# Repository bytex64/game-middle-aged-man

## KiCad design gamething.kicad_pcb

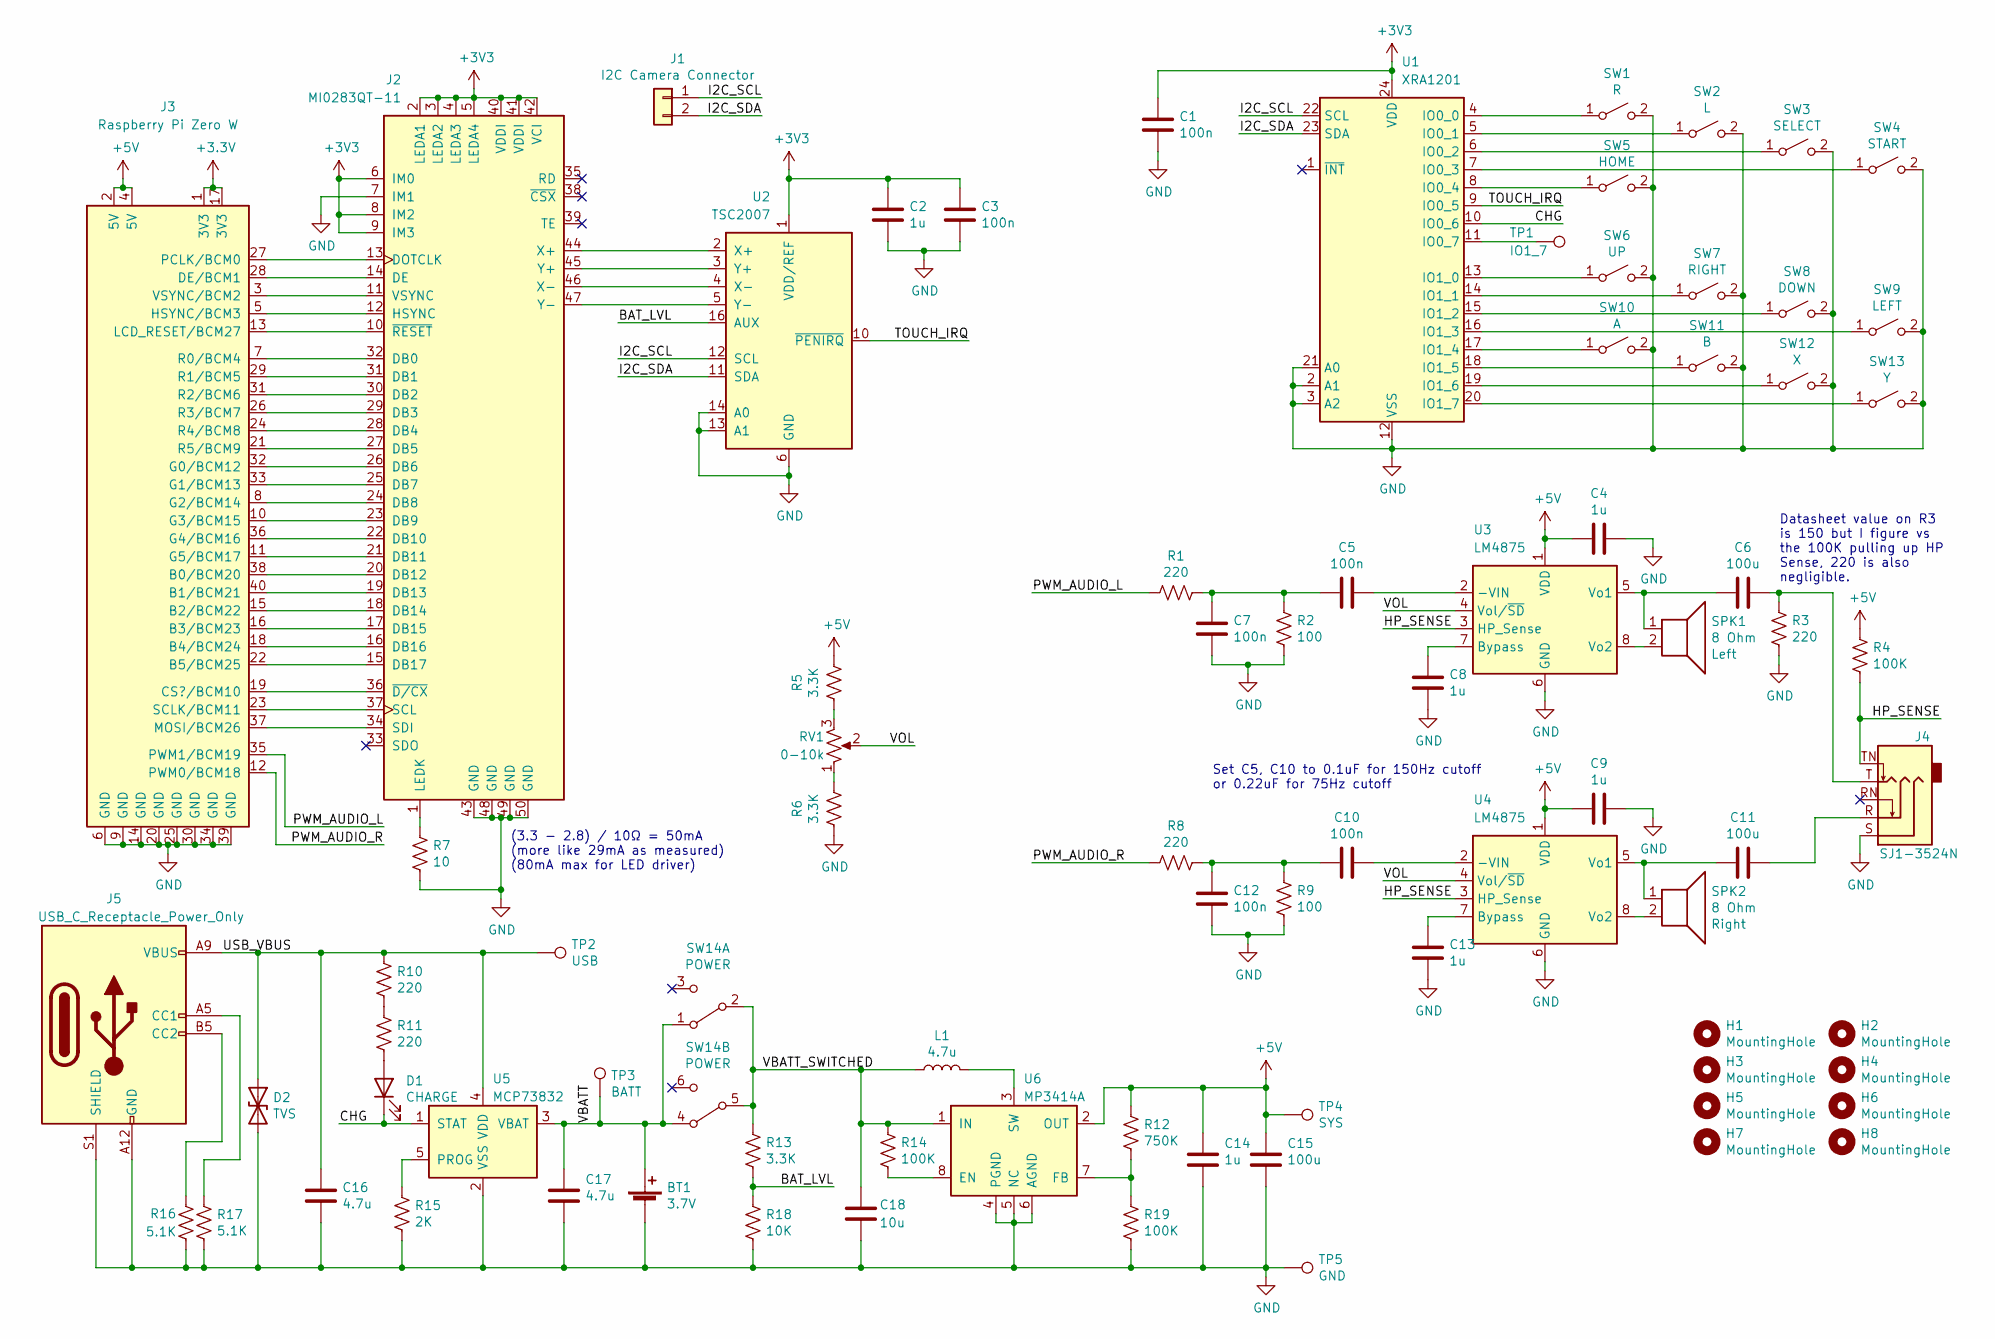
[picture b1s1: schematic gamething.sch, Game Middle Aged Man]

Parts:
BT1: 3.7V; JST_PH_S2B-PH-K_1x02_P2.00mm_Horizontal; MPN Harwin M22-2210246 or TE 440055-2
C1, C3, C5, C7, C10, C12: 100n; C_0805_2012Metric_Pad1.15x1.40mm_HandSolder; MPN CL21B104KACNNNC
C2, C4, C8, C9, C13, C14: 1u; C_0805_2012Metric_Pad1.15x1.40mm_HandSolder; MPN C0805C105K4RACTU
C6, C11, C15: 100u; C_1206_3216Metric_Pad1.42x1.75mm_HandSolder; MPN JMK316ABJ107ML-T
C16, C17: 4.7u; C_0805_2012Metric_Pad1.15x1.40mm_HandSolder; MPN CL21A475KPFNNNE
C18: 10u; C_0805_2012Metric_Pad1.15x1.40mm_HandSolder; MPN C0805C106K8PACTU
D1: CHARGE; LED_D3.0mm; MPN LTL-4221N
D2: TVS; D_SOD-323_HandSoldering; MPN DF2B7AFU,H3F
H1, H2, H3, H4, H5, H6, H7, H8: MountingHole; MountingHole_2.7mm_M2.5
J1: I2C Camera Connector; PinHeader_1x02_P2.54mm_Vertical
J2: MI0283QT-11; MI0283QT-11_tucked_connector; MPN 62684-50210E9ALF
J3: Raspberry Pi Zero W; Raspberry_Pi_Zero_Socketed_THT_FaceDown_MountingHoles
J4: SJ1-3524N; SJ1-3525N; MPN SJ1-3524N
J5: USB_C_Receptacle_Power_Only; UJC-HP-3-SMT; MPN UJC-HP-3-SMT
L1: 4.7u; L_6x6_H4.5_Handsoldering; MPN TYS60454R7M-10
R1, R3, R8, R10, R11: 220; R_0805_2012Metric_Pad1.15x1.40mm_HandSolder; MPN RK73B2ATTD221J
R2, R9: 100; R_0805_2012Metric_Pad1.15x1.40mm_HandSolder; MPN RK73H2ATTE1000F
R4, R14, R19: 100K; R_0805_2012Metric_Pad1.15x1.40mm_HandSolder; MPN CR0805AFX-1003ELF
R5, R6, R13: 3.3K; R_0805_2012Metric_Pad1.15x1.40mm_HandSolder; MPN CR0805-FX-3301ELF
R7: 10; R_Axial_DIN0207_L6.3mm_D2.5mm_P7.62mm_Horizontal
R12: 750K; R_0805_2012Metric_Pad1.15x1.40mm_HandSolder
R15: 2K; R_0805_2012Metric_Pad1.15x1.40mm_HandSolder; MPN CR0805-FX-2001ELF
R16, R17: 5.1K; R_0805_2012Metric_Pad1.15x1.40mm_HandSolder; MPN RK73B2ATTD512J
R18: 10K; R_0805_2012Metric_Pad1.15x1.40mm_HandSolder; MPN RK73H2ATTD1002F
RV1: 0-10k; RK10J11E; MPN RK10J11E0034
SPK1, SPK2: 8 Ohm; PinHeader_1x02_P2.54mm_Vertical; MPN SM300408-4
SW1: R; B3F-3100; MPN B3F-3100
SW2: L; B3F-3100; MPN B3F-3100
SW3: SELECT; B3F-1000_2terminal; MPN B3F-1000
SW4: START; B3F-1000_2terminal; MPN B3F-1000
SW5: HOME; B3F-1000_2terminal; MPN B3F-1000
SW6: UP; B3F-1000_2terminal; MPN B3F-1000
SW7: RIGHT; B3F-1000_2terminal; MPN B3F-1000
SW8: DOWN; B3F-1000_2terminal; MPN B3F-1000
SW9: LEFT; B3F-1000_2terminal; MPN B3F-1000
SW10: A; B3F-1000_2terminal; MPN B3F-1000
SW11: B; B3F-1000_2terminal; MPN B3F-1000
SW12: X; B3F-1000_2terminal; MPN B3F-1000
SW13: Y; B3F-1000_2terminal; MPN B3F-1000
SW14: POWER; JS202011AQN; MPN JS202011AQN
TP1: IO1_7; TestPoint_THTPad_D1.5mm_Drill0.9mm
TP2: USB; TestPoint_THTPad_D1.5mm_Drill0.9mm
TP3: BATT; TestPoint_THTPad_D1.5mm_Drill0.9mm
TP4: SYS; TestPoint_THTPad_D1.5mm_Drill0.9mm
TP5: GND; TestPoint_THTPad_D1.5mm_Drill0.9mm
U1: XRA1201; TSSOP-24_4.4x7.8mm_P0.65mm; MPN XRA1201PIG24TR-F
U2: TSC2007; TSSOP-16_4.4x5mm_P0.65mm; MPN TSC2007IPWR
U3, U4: LM4875; SOIC-8_3.9x4.9mm_P1.27mm; MPN LM4875MX/NOPB
U5: MCP73832; SOT-23-5; MPN MCP73832T-2ACI/OT
U6: MP3414A; TSOT-23-8; MPN MP3414AGJ-Z

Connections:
+5V: C4.2, C9.2, C14.1, C15.1, J3.2 (5V), J3.4 (5V), R4.2, R5.1, R12.1, TP4.1, U3.1 (VDD), U4.1 (VDD), U6.2 (OUT)
/BAT_LVL: R13.2, R18.1, U2.16 (AUX)
/CHG: D1.1 (K), U1.10 (IO0_6), U5.1 (STAT)
/HP_SENSE: J4.TN, R4.1, U3.3 (HP_Sense), U4.3 (HP_Sense)
/I2C_SCL: J1.1, U1.22 (SCL), U2.12 (SCL)
/I2C_SDA: J1.2, U1.23 (SDA), U2.11 (SDA)
/PWM_AUDIO_L: J3.35 (PWM1/BCM19), R1.2
/PWM_AUDIO_R: J3.12 (PWM0/BCM18), R8.2
/TOUCH_IRQ: U1.9 (IO0_5), U2.10 (~PENIRQ)
/USB_VBUS: C16.1, D2.1 (A1), J5.A9 (VBUS), J5.B9 (VBUS), R10.1, TP2.1, U5.4 (VDD)
/VBATT: BT1.1 (+), C17.1, SW14.1 (A), SW14.4 (A), TP3.1, U5.3 (VBAT)
/VBATT_SWITCHED: C18.1, L1.1, R13.1, R14.1, SW14.2 (B), SW14.5 (B), U6.1 (IN)
/VOL: RV1.2, U3.4 (Vol/~SD), U4.4 (Vol/~SD)
GND: BT1.2 (-), C1.2, C2.2, C3.2, C4.1, C7.2, C8.2, C9.1, C12.2, C13.2, C14.2, C15.2, C16.2, C17.2, C18.2, D2.2 (A2), J2.7 (IM1), J2.43 (GND), J2.48 (GND), J2.49 (GND), J2.50 (GND), J3.6 (GND), J3.9 (GND), J3.14 (GND), J3.20 (GND), J3.25 (GND), J3.30 (GND), J3.34 (GND), J3.39 (GND), J4.S, J5.A12 (GND), J5.B12 (GND), J5.S1 (SHIELD), R2.1, R3.1, R6.2, R7.2, R9.1, R15.2, R16.2, R17.2, R18.2, R19.2, SW1.2 (B), SW2.2 (B), SW3.2 (B), SW4.2 (B), SW5.2 (B), SW6.2 (B), SW7.2 (B), SW8.2 (B), SW9.2 (B), SW10.2 (B), SW11.2 (B), SW12.2 (B), SW13.2 (B), TP5.1, U1.2 (A1), U1.3 (A2), U1.12 (VSS), U1.21 (A0), U2.6 (GND), U2.13 (A1), U2.14 (A0), U3.6 (GND), U4.6 (GND), U5.2 (VSS), U6.4 (PGND), U6.5 (NC), U6.6 (AGND)
unnamed: C5.1, U3.2 (-VIN)
unnamed: C5.2, C7.1, R1.1, R2.2
unnamed: C6.1, J4.T, R3.2
unnamed: C6.2, SPK1.1, U3.5 (Vo1)
unnamed: C8.1, U3.7 (Bypass)
unnamed: C10.1, U4.2 (-VIN)
unnamed: C10.2, C12.1, R8.1, R9.2
unnamed: C11.1, J4.R
unnamed: C11.2, SPK2.1, U4.5 (Vo1)
unnamed: C13.1, U4.7 (Bypass)
unnamed: D1.2 (A), R11.2
unnamed: J2.1 (LEDK), R7.1
unnamed: J2.10 (~RESET), J3.13 (LCD_RESET/BCM27)
unnamed: J2.11 (VSYNC), J3.3 (VSYNC/BCM2)
unnamed: J2.12 (HSYNC), J3.5 (HSYNC/BCM3)
unnamed: J2.13 (DOTCLK), J3.27 (PCLK/BCM0)
unnamed: J2.14 (DE), J3.28 (DE/BCM1)
unnamed: J2.15 (DB17), J3.22 (B5/BCM25)
unnamed: J2.16 (DB16), J3.18 (B4/BCM24)
unnamed: J2.17 (DB15), J3.16 (B3/BCM23)
unnamed: J2.18 (DB14), J3.15 (B2/BCM22)
unnamed: J2.19 (DB13), J3.40 (B1/BCM21)
unnamed: J2.20 (DB12), J3.38 (B0/BCM20)
unnamed: J2.21 (DB11), J3.11 (G5/BCM17)
unnamed: J2.22 (DB10), J3.36 (G4/BCM16)
unnamed: J2.23 (DB9), J3.10 (G3/BCM15)
unnamed: J2.24 (DB8), J3.8 (G2/BCM14)
unnamed: J2.25 (DB7), J3.33 (G1/BCM13)
unnamed: J2.26 (DB6), J3.32 (G0/BCM12)
unnamed: J2.27 (DB5), J3.21 (R5/BCM9)
unnamed: J2.28 (DB4), J3.24 (R4/BCM8)
unnamed: J2.29 (DB3), J3.26 (R3/BCM7)
unnamed: J2.30 (DB2), J3.31 (R2/BCM6)
unnamed: J2.31 (DB1), J3.29 (R1/BCM5)
unnamed: J2.32 (DB0), J3.7 (R0/BCM4)
unnamed: J2.34 (SDI), J3.37 (MOSI/BCM26)
unnamed: J2.36 (~D/CX), J3.19 (CS?/BCM10)
unnamed: J2.37 (SCL), J3.23 (SCLK/BCM11)
unnamed: J2.44 (X+), U2.2 (X+)
unnamed: J2.45 (Y+), U2.3 (Y+)
unnamed: J2.46 (X-), U2.4 (X-)
unnamed: J2.47 (Y-), U2.5 (Y-)
unnamed: J5.A5 (CC1), R17.1
unnamed: J5.B5 (CC2), R16.1
unnamed: L1.2, U6.3 (SW)
unnamed: R5.2, RV1.3
unnamed: R6.1, RV1.1
unnamed: R10.2, R11.1
unnamed: R12.2, R19.1, U6.7 (FB)
unnamed: R14.2, U6.8 (EN)
unnamed: R15.1, U5.5 (PROG)
unnamed: SPK1.2, U3.8 (Vo2)
unnamed: SPK2.2, U4.8 (Vo2)
unnamed: SW1.1 (A), U1.4 (IO0_0)
unnamed: SW2.1 (A), U1.5 (IO0_1)
unnamed: SW3.1 (A), U1.6 (IO0_2)
unnamed: SW4.1 (A), U1.7 (IO0_3)
unnamed: SW5.1 (A), U1.8 (IO0_4)
unnamed: SW6.1 (A), U1.13 (IO1_0)
unnamed: SW7.1 (A), U1.14 (IO1_1)
unnamed: SW8.1 (A), U1.15 (IO1_2)
unnamed: SW9.1 (A), U1.16 (IO1_3)
unnamed: SW10.1 (A), U1.17 (IO1_4)
unnamed: SW11.1 (A), U1.18 (IO1_5)
unnamed: SW12.1 (A), U1.19 (IO1_6)
unnamed: SW13.1 (A), U1.20 (IO1_7)
unnamed: TP1.1, U1.11 (IO0_7)

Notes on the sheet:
(3.3 - 2.8) / 10Ω = 50mA (more like 29mA as measured) (80mA max for LED driver)
Set C5, C10 to 0.1uF for 150Hz cutoff or 0.22uF for 75Hz cutoff
Datasheet value on R3 is 150 but I figure vs the 100K pulling up HP Sense, 220 is also negligible.

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
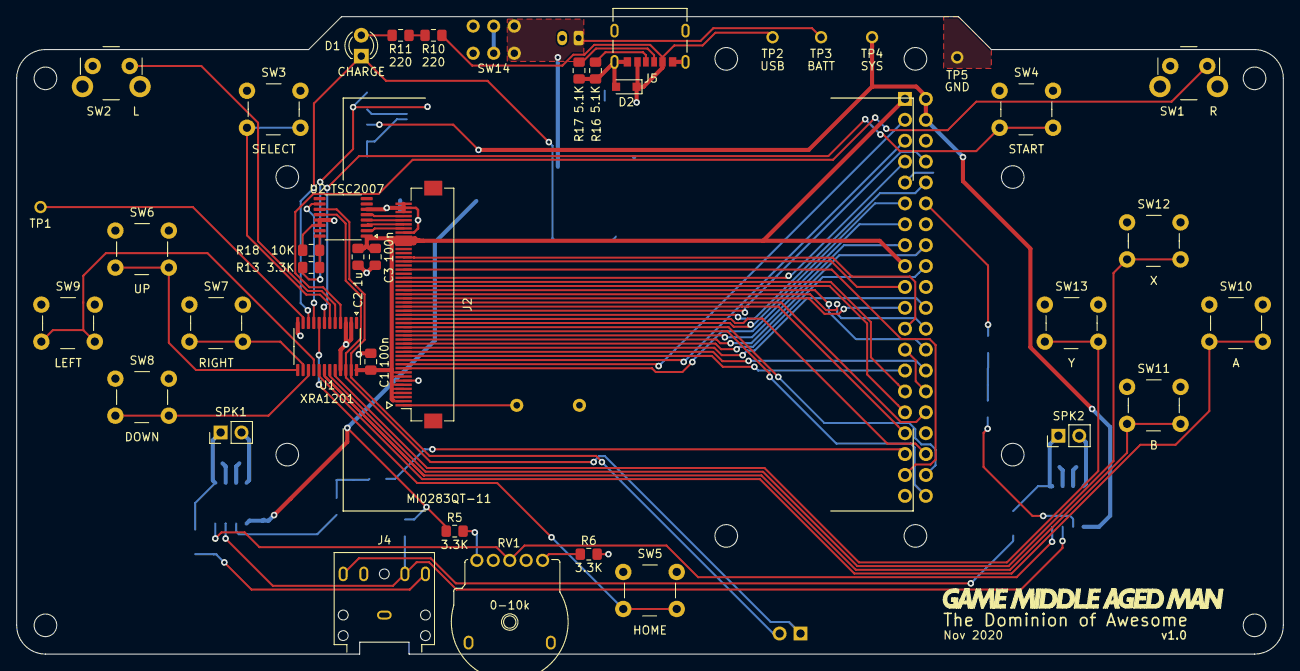
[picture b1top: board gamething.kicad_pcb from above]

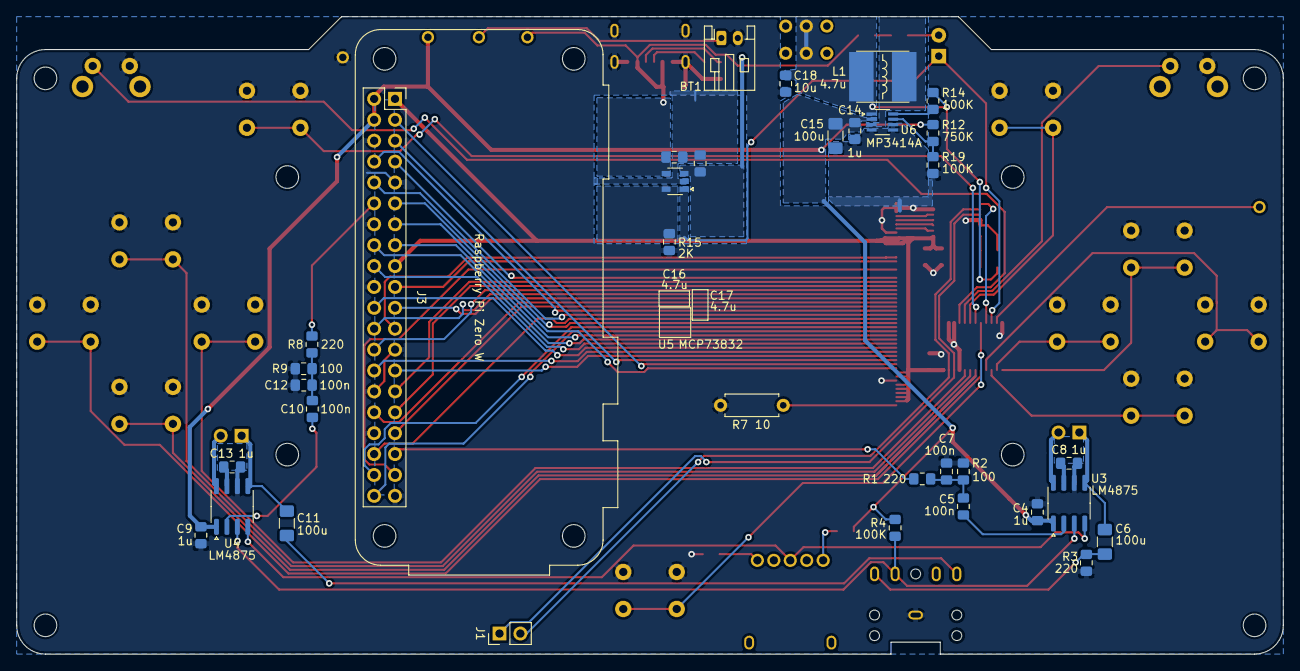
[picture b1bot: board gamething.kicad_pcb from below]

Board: 2 copper layers, 154.0 x 77.5 mm, 82 parts (34 on the bottom side), 82 nets.

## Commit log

2020-11-22 Add logo to board
2020-11-22 Post-release updates
